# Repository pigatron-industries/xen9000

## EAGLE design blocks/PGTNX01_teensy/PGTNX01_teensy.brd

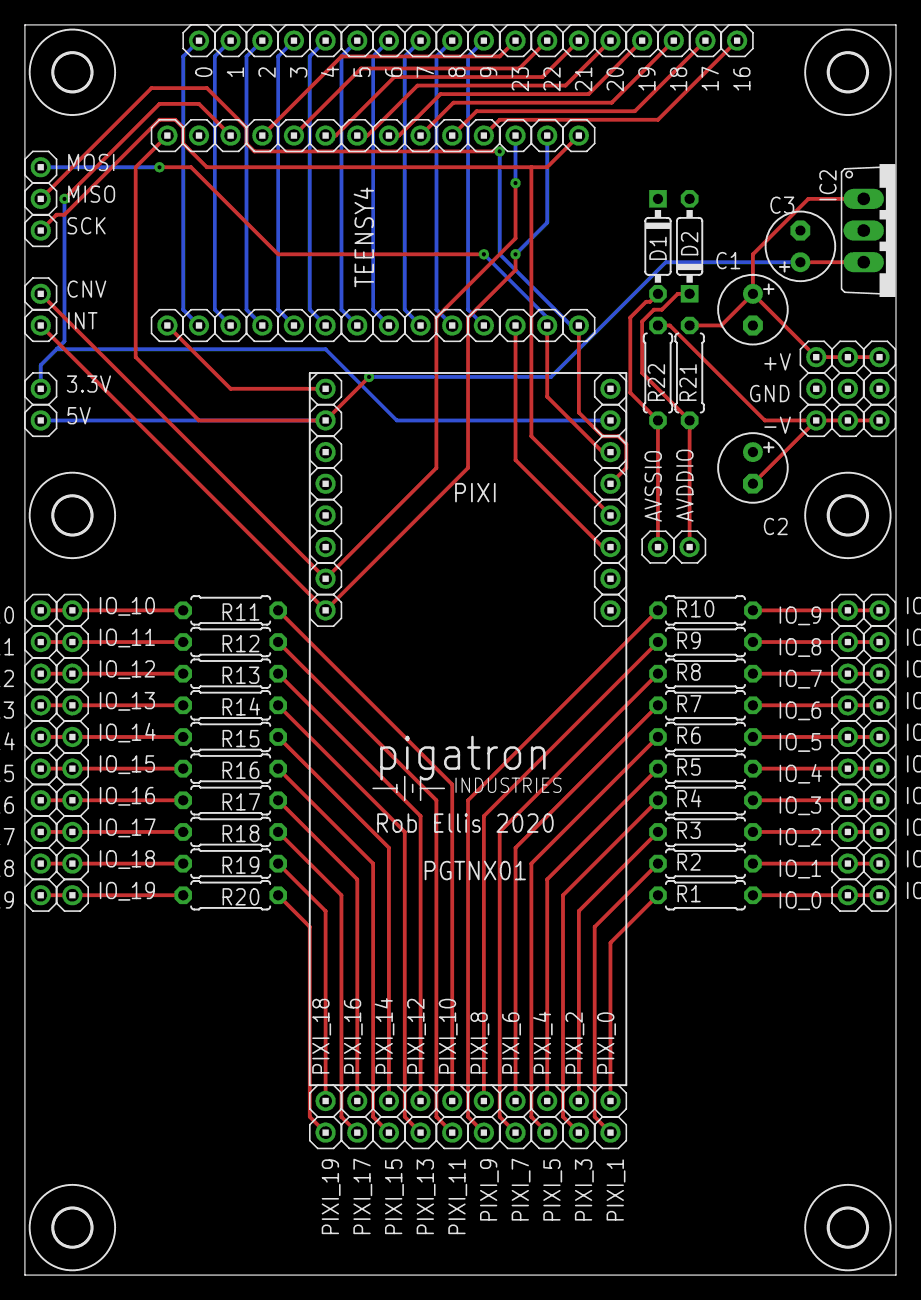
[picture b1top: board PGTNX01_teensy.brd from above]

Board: 2 copper layers, 69.9 x 100.3 mm, 175 parts (0 on the bottom side), 71 nets.

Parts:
0, 1, 2, 3, 3.3V, 4, 5, 5V, 6, 7, 8, 9, 16, 17, 18, 19, 20, 21, 22, 23: HEADER/MALE/01
+V, +V2, +V3: HEADER/MALE/01
-V, -V2, -V3: HEADER/MALE/01
AVDDIO: HEADER/MALE/01
AVSSIO: HEADER/MALE/01
C1, C2: 10uF; E2,5-6
C3: 0.1uF; E2,5-6
CNV: HEADER/MALE/01
D1, D2: DO35-7
GND, GND2, GND3: HEADER/MALE/01
IC2: 7805TV; TO220V
INT: HEADER/MALE/01
IO_0, IO_1, IO_2, IO_3, IO_4, IO_5, IO_6, IO_7, IO_8, IO_9, IO_10, IO_11, IO_12, IO_13, IO_14, IO_15, IO_16, IO_17, IO_18, IO_19: HEADER/MALE/01
IO__0, IO__1, IO__2, IO__3, IO__4, IO__5, IO__6, IO__7, IO__8, IO__9, IO__10, IO__11, IO__12, IO__13, IO__14, IO__15, IO__16, IO__17, IO__18, IO__19: HEADER/MALE/01
MISO: HEADER/MALE/01
MOSI: HEADER/MALE/01
PIXI_0, PIXI_1, PIXI_2, PIXI_3, PIXI_3.3V, PIXI_4, PIXI_5, PIXI_5V, PIXI_6, PIXI_7, PIXI_8, PIXI_9, PIXI_10, PIXI_11, PIXI_12, PIXI_13, PIXI_14, PIXI_15, PIXI_16, PIXI_17, PIXI_18, PIXI_19: HEADER/MALE/01
PIXI_CNV: HEADER/MALE/01
PIXI_CS: HEADER/MALE/01
PIXI_GND, PIXI_GND2: HEADER/MALE/01
PIXI_INT: HEADER/MALE/01
PIXI_NC1, PIXI_NC2, PIXI_NC3, PIXI_NC4, PIXI_NC5, PIXI_NC6: HEADER/MALE/01
PIXI_SCK: HEADER/MALE/01
PIXI_SDI: HEADER/MALE/01
PIXI_SDO: HEADER/MALE/01
R1, R2, R3, R4, R5, R6, R7, R8, R9, R10, R11, R12, R13, R14, R15, R16, R17, R18, R19, R20, R21, R22: RESISTOR/7.5
SCK: HEADER/MALE/01
TNSY_0, TNSY_1, TNSY_2, TNSY_3, TNSY_3.3V, TNSY_4, TNSY_5, TNSY_6, TNSY_7, TNSY_8, TNSY_9, TNSY_14, TNSY_15, TNSY_16, TNSY_17, TNSY_18, TNSY_19, TNSY_20, TNSY_21, TNSY_22, TNSY_23: HEADER/MALE/01
TNSY_CS: HEADER/MALE/01
TNSY_GND, TNSY_GND2: HEADER/MALE/01
TNSY_MISO: HEADER/MALE/01
TNSY_MOSI: HEADER/MALE/01
TNSY_SCK: HEADER/MALE/01
TNSY_VIN: HEADER/MALE/01
U$1, U$2, U$3, U$4, U$6, U$7: STANDOFF/3.0
U$5: PIGATRON-LOGO

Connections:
+5V: 5V.1, C3.+, IC2.3, PIXI_5V.1, TNSY_VIN.1
+12V: +V.1, +V2.1, +V3.1, C1.+, IC2.1, R21.2
-12V: -V.1, -V2.1, -V3.1, C2.-, R22.2
GND: C1.-, C2.+, C3.-, D1.C, D2.A, GND.1, GND2.1, GND3.1, IC2.2, PIXI_GND.1, PIXI_GND2.1, TNSY_GND.1
unnamed: PIXI_0.1, R1.1
unnamed: 17.1, TNSY_17.1
unnamed: PIXI_1.1, R2.1
unnamed: 16.1, TNSY_16.1
unnamed: MOSI.1, PIXI_SDI.1, TNSY_MOSI.1
unnamed: MISO.1, PIXI_SDO.1, TNSY_MISO.1
unnamed: PIXI_SCK.1, SCK.1, TNSY_SCK.1
unnamed: PIXI_CS.1, TNSY_CS.1
unnamed: INT.1, PIXI_CNV.1, TNSY_14.1
unnamed: CNV.1, PIXI_INT.1, TNSY_15.1
unnamed: 18.1, TNSY_18.1
unnamed: 19.1, TNSY_19.1
unnamed: 20.1, TNSY_20.1
unnamed: 21.1, TNSY_21.1
unnamed: 22.1, TNSY_22.1
unnamed: 23.1, TNSY_23.1
unnamed: 0.1, TNSY_0.1
unnamed: 1.1, TNSY_1.1
unnamed: 2.1, TNSY_2.1
unnamed: 3.1, TNSY_3.1
unnamed: 4.1, TNSY_4.1
unnamed: 5.1, TNSY_5.1
unnamed: 6.1, TNSY_6.1
unnamed: 7.1, TNSY_7.1
unnamed: 8.1, TNSY_8.1
unnamed: 9.1, TNSY_9.1
unnamed: IO_1.1, IO__1.1, R2.2
unnamed: 3.3V.1, PIXI_3.3V.1, TNSY_3.3V.1
unnamed: IO_0.1, IO__0.1, R1.2
unnamed: PIXI_2.1, R3.1
unnamed: IO_2.1, IO__2.1, R3.2
unnamed: PIXI_3.1, R4.1
unnamed: IO_3.1, IO__3.1, R4.2
unnamed: PIXI_4.1, R5.1
unnamed: IO_4.1, IO__4.1, R5.2
unnamed: PIXI_5.1, R6.1
unnamed: IO_5.1, IO__5.1, R6.2
unnamed: PIXI_6.1, R7.1
unnamed: IO_6.1, IO__6.1, R7.2
unnamed: PIXI_7.1, R8.1
unnamed: IO_7.1, IO__7.1, R8.2
unnamed: PIXI_8.1, R9.1
unnamed: IO_8.1, IO__8.1, R9.2
unnamed: PIXI_9.1, R10.1
unnamed: IO_9.1, IO__9.1, R10.2
unnamed: PIXI_10.1, R11.1
unnamed: IO_10.1, IO__10.1, R11.2
unnamed: PIXI_11.1, R12.1
unnamed: IO_11.1, IO__11.1, R12.2
unnamed: PIXI_12.1, R13.1
unnamed: IO_12.1, IO__12.1, R13.2
unnamed: PIXI_13.1, R14.1
unnamed: IO_13.1, IO__13.1, R14.2
unnamed: PIXI_14.1, R15.1
unnamed: IO_14.1, IO__14.1, R15.2
unnamed: PIXI_15.1, R16.1
unnamed: IO_15.1, IO__15.1, R16.2
unnamed: PIXI_16.1, R17.1
unnamed: IO_16.1, IO__16.1, R17.2
unnamed: PIXI_17.1, R18.1
unnamed: IO_17.1, IO__17.1, R18.2
unnamed: PIXI_18.1, R19.1
unnamed: IO_18.1, IO__18.1, R19.2
unnamed: PIXI_19.1, R20.1
unnamed: IO_19.1, IO__19.1, R20.2
unnamed: AVDDIO.1, D2.C, R21.1
unnamed: AVSSIO.1, D1.A, R22.1

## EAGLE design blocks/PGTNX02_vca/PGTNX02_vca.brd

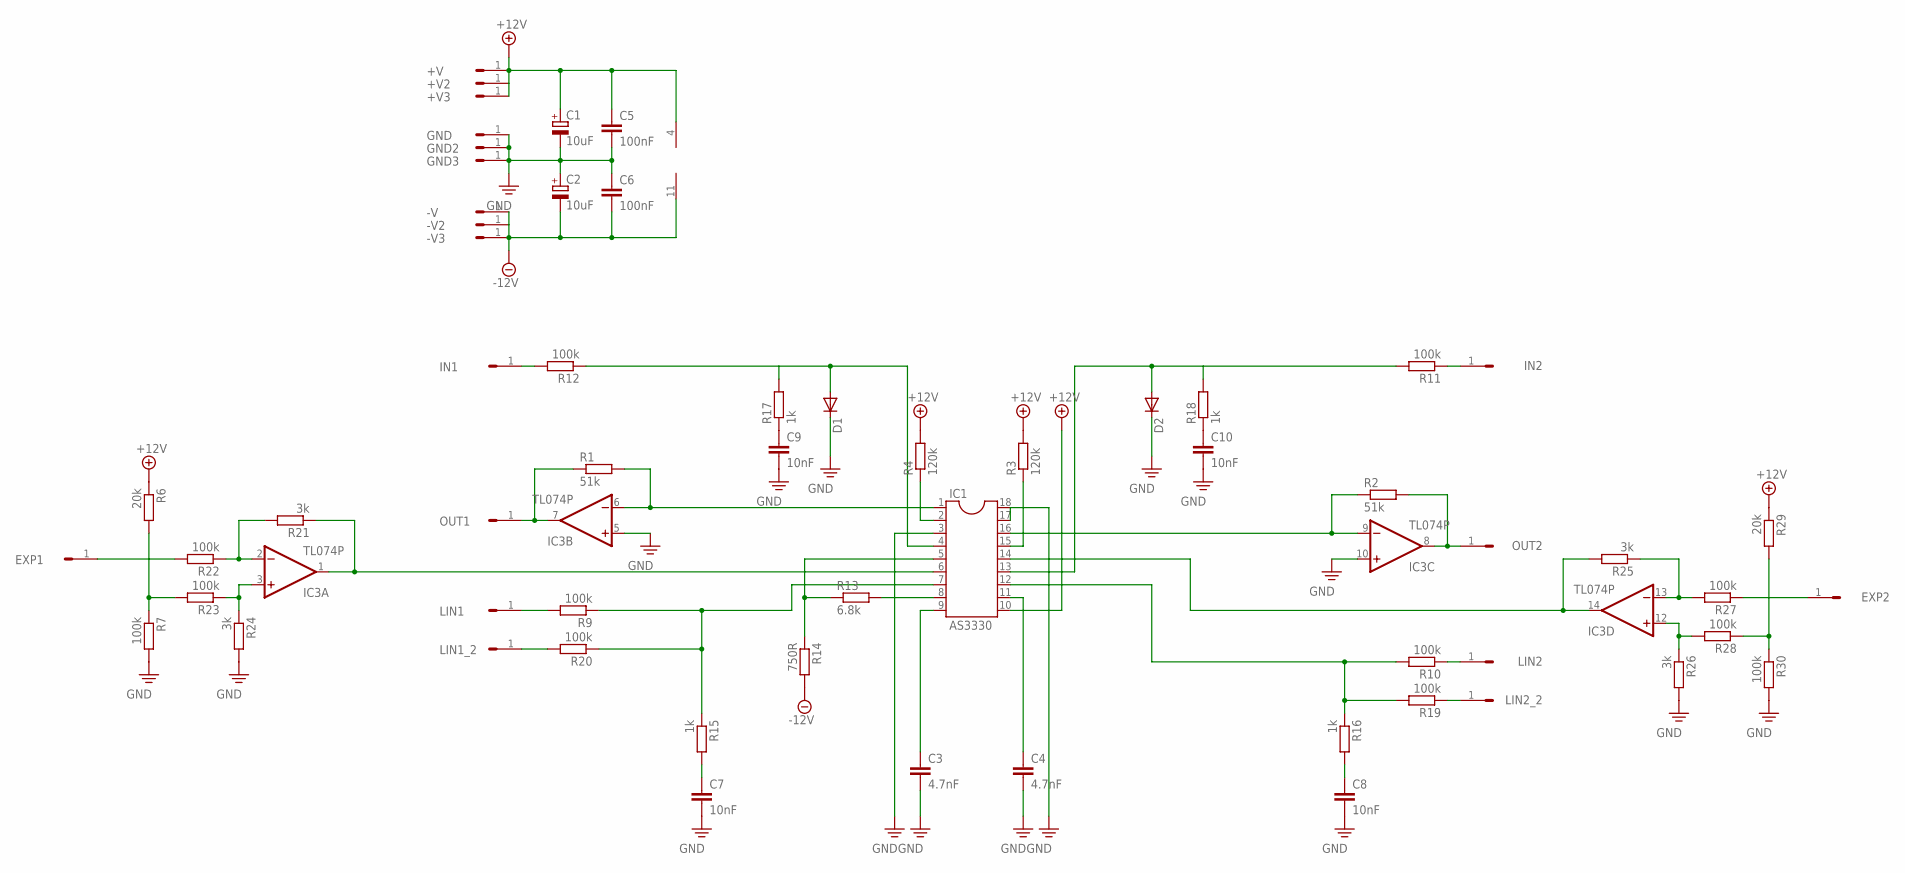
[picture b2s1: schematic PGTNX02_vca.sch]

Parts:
+V, +V2, +V3: HEADER/MALE/01
-V, -V2, -V3: HEADER/MALE/01
C1, C2: 10uF; E2,5-6
C3, C4: 4.7nF; CERAMICDISC/5
C5, C6: 100nF; CERAMICDISC/5
C7, C8, C9, C10: 10nF; CERAMICDISC/5
D1, D2: 1N4148DO35-7; DO35-7
EXP1, EXP2: HEADER/MALE/01
GND, GND2, GND3: HEADER/MALE/01
IC1: AS3330; DIL18
IC3: TL074P; DIL14
IN1, IN2: HEADER/MALE/01
LIN1, LIN1_2, LIN2, LIN2_2: HEADER/MALE/01
OUT1, OUT2: HEADER/MALE/01
R1, R2: 51k; RESISTOR/7.5
R3, R4: 120k; RESISTOR/7.5
R6, R29: 20k; RESISTOR/7.5
R7, R9, R10, R11, R12, R19, R20, R22, R23, R27, R28, R30: 100k; RESISTOR/7.5
R13: 6.8k; RESISTOR/7.5
R14: 750R; RESISTOR/7.5
R15, R16, R17, R18: 1k; RESISTOR/7.5
R21, R24, R25, R26: 3k; RESISTOR/7.5

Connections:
+12V: +V.1, +V2.1, +V3.1, C1.+, C5.1, IC1.10, IC3.4 (V+), R3.2, R4.2, R6.1, R29.1
-12V: -V.1, -V2.1, -V3.1, C2.-, C6.2, IC3.11 (V-), R14.2
unnamed: IC1.1, IC3.6 (-IN), R1.2
unnamed: IC3.7 (OUT), OUT1.1, R1.1
unnamed: IC1.16, IC3.9 (-IN), R2.1
unnamed: IC3.8 (OUT), OUT2.1, R2.2
unnamed: C4.1, IC1.11
unnamed: IC1.15, R3.1
unnamed: IC1.2, R4.1
unnamed: C3.1, IC1.9
unnamed: IC1.14, IC3.14 (OUT), R25.2
unnamed: IC1.6, IC3.1 (OUT), R21.1
unnamed: EXP1.1, R22.2
unnamed: EXP2.1, R27.1
unnamed: IC1.7, R9.1, R15.1, R20.1
unnamed: IC1.12, R10.2, R16.1, R19.2
unnamed: LIN2.1, R10.1
unnamed: LIN1.1, R9.2
unnamed: D2.A, IC1.13, R11.2, R18.2
unnamed: D1.A, IC1.4, R12.1, R17.2
unnamed: IN1.1, R12.2
unnamed: IN2.1, R11.1
unnamed: IC1.5, R13.1, R14.1
unnamed: IC1.8, R13.2
unnamed: C7.1, R15.2
unnamed: C8.1, R16.2
unnamed: C9.1, R17.1
unnamed: C10.1, R18.1
unnamed: LIN1_2.1, R20.2
unnamed: LIN2_2.1, R19.1
unnamed: R6.2, R7.1, R23.2
unnamed: IC3.2 (-IN), R21.2, R22.1
unnamed: IC3.3 (+IN), R23.1, R24.1
unnamed: IC3.13 (-IN), R25.1, R27.2
unnamed: IC3.12 (+IN), R26.1, R28.2
unnamed: R28.1, R29.2, R30.1
PE: C1.-, C2.+, C3.2, C4.2, C5.2, C6.1, C7.2, C8.2, C9.2, C10.2, D1.C, D2.C, GND.1, GND2.1, GND3.1, IC1.3, IC1.17, IC1.18, IC3.5 (+IN), IC3.10 (+IN), R7.2, R24.2, R26.2, R30.2

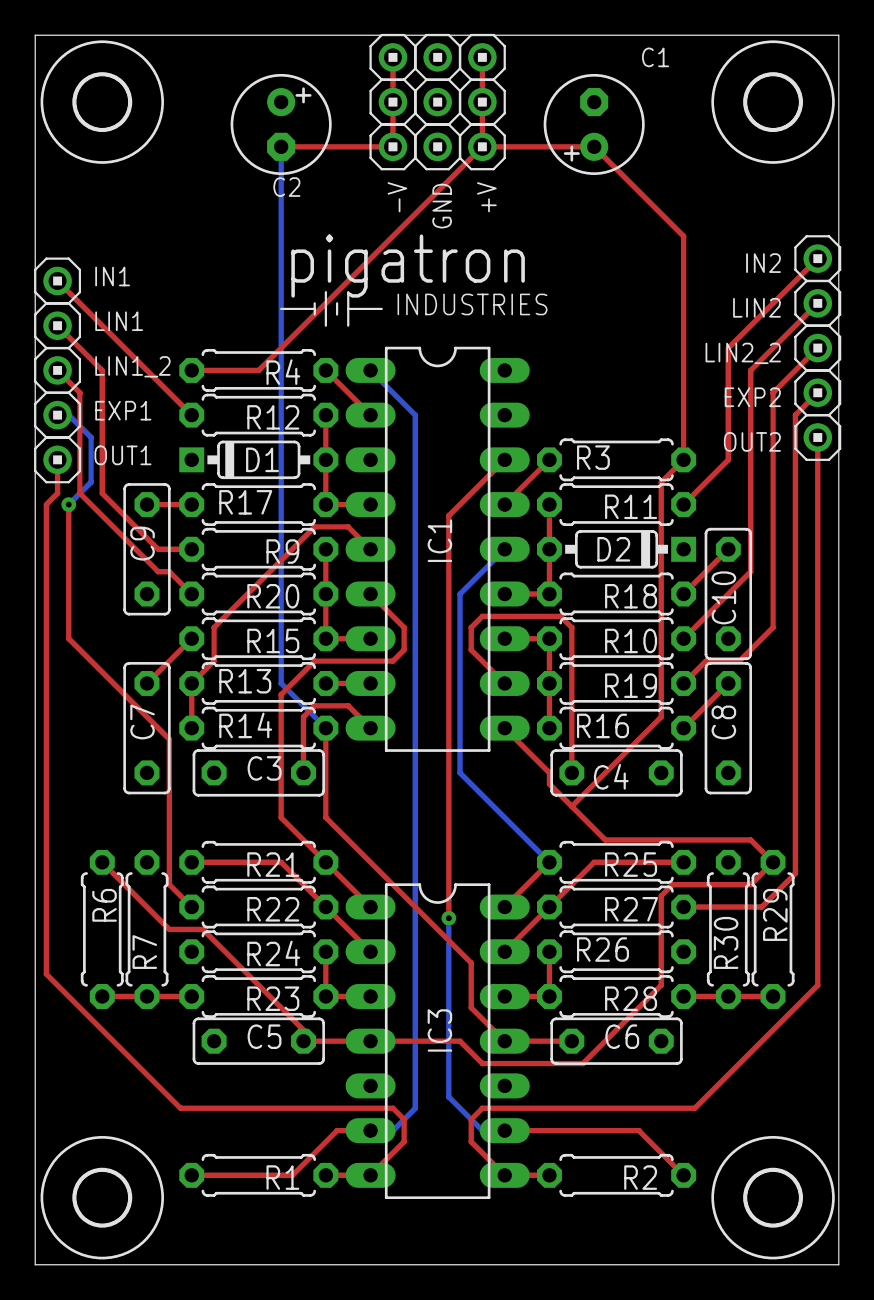
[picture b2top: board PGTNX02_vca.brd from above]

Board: 2 copper layers, 45.6 x 69.8 mm, 66 parts (0 on the bottom side), 37 nets.

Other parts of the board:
U$1, U$2, U$3, U$4: STANDOFF/3.0
U$5: PIGATRON-LOGO

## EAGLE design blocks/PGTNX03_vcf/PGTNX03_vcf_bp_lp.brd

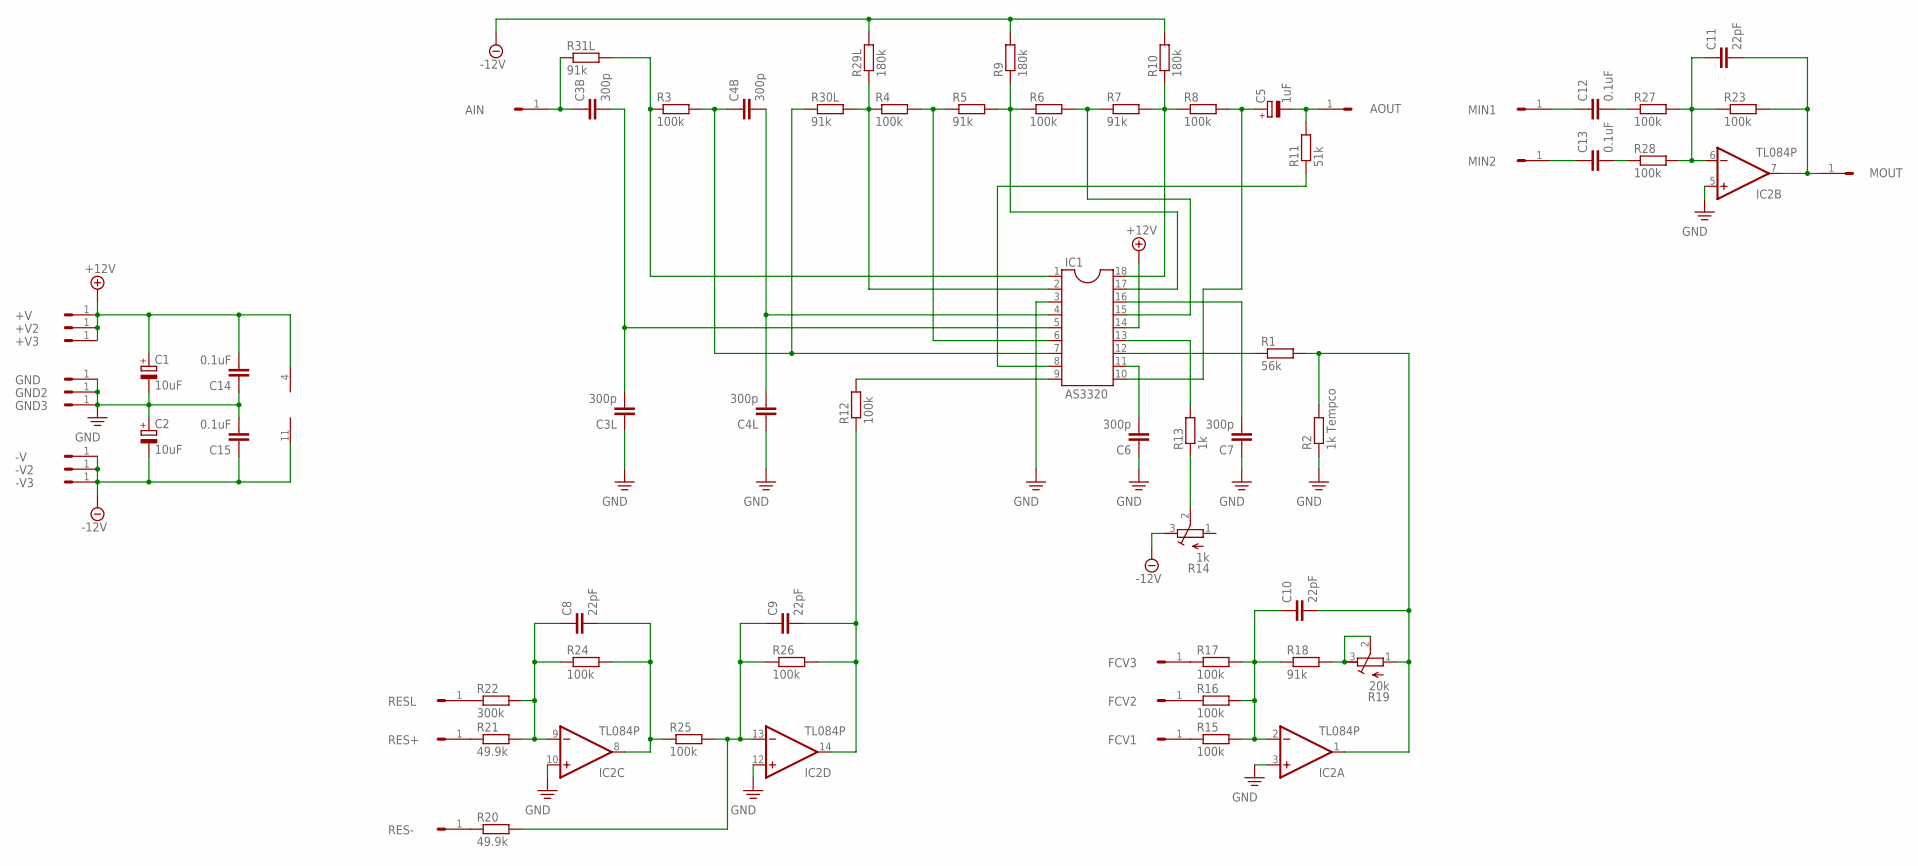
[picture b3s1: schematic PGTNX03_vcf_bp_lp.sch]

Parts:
+V, +V2, +V3: HEADER/MALE/01
-V, -V2, -V3: HEADER/MALE/01
AIN: HEADER/MALE/01
AOUT: HEADER/MALE/01
C1, C2: 10uF; E2,5-6
C3B, C3L, C4B, C4L, C6, C7: 300p; CERAMICDISC/5
C5: 1uF; E2,5-6
C8, C9, C10, C11: 22pF; CERAMICDISC/5
C12, C13, C14, C15: 0.1uF; CERAMICDISC/5
FCV1, FCV2, FCV3: HEADER/MALE/01
GND, GND2, GND3: HEADER/MALE/01
IC1: AS3320; DIL18
IC2: TL084P; DIL14
MIN1, MIN2: HEADER/MALE/01
MOUT: HEADER/MALE/01
R1: 56k; RESISTOR/7.5
R2: 1k Tempco; RESISTOR/7.5
R3, R4, R6, R8, R12, R15, R16, R17, R23, R24, R25, R26, R27, R28: 100k; RESISTOR/7.5
R5, R7, R18, R30L, R31L: 91k; RESISTOR/7.5
R9, R10, R29L: 180k; RESISTOR/7.5
R11: 51k; RESISTOR/7.5
R13: 1k; RESISTOR/7.5
R14: 1k; TRIMMER/64B
R19: 20k; TRIMMER/64B
R20, R21: 49.9k; RESISTOR/7.5
R22: 300k; RESISTOR/7.5
RES+: HEADER/MALE/01
RES-: HEADER/MALE/01
RESL: HEADER/MALE/01

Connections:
+12V: +V.1, +V2.1, +V3.1, C1.+, C14.2, IC1.14, IC2.4 (V+)
-12V: -V.1, -V2.1, -V3.1, C2.-, C15.1, IC2.11 (V-), R9.2, R10.2, R14.3 (A), R29L.2
GND: C1.-, C2.+, C3L.1, C4L.1, C6.1, C7.1, C14.1, C15.2, GND.1, GND2.1, GND3.1, IC1.3, IC2.3 (+IN), IC2.5 (+IN), IC2.10 (+IN), IC2.12 (+IN), R2.1
MOUT: C11.2, IC2.7 (OUT), MOUT.1, R23.2
unnamed: C3B.2, C3L.2, IC1.5
unnamed: AIN.1, C3B.1, R31L.1
unnamed: IC1.12, R1.1
unnamed: R20.1, RES-.1
unnamed: C4B.1, IC1.7, R3.2, R30L.1
unnamed: IC1.6, R4.2, R5.1
unnamed: IC1.17, R5.2, R6.1, R9.1
unnamed: IC1.15, R6.2, R7.1
unnamed: IC1.18, R7.2, R8.1, R10.1
unnamed: IC1.9, R12.2
unnamed: C5.+, IC1.10, R8.2
unnamed: AOUT.1, C5.-, R11.2
unnamed: R18.2, R19.2 (S), R19.3 (A)
unnamed: C6.2, IC1.11
unnamed: C7.2, IC1.16
unnamed: FCV2.1, R16.1
unnamed: FCV3.1, R17.1
unnamed: IC1.13, R13.2
unnamed: R13.1, R14.2 (S)
unnamed: IC1.1, R3.1, R31L.2
unnamed: C4B.2, C4L.2, IC1.4
unnamed: IC1.2, R4.1, R29L.1, R30L.2
unnamed: IC1.8, R11.1
unnamed: C10.2, IC2.1 (OUT), R1.2, R2.2, R19.1 (E)
unnamed: C10.1, IC2.2 (-IN), R15.2, R16.2, R17.2, R18.1
unnamed: C12.2, R27.1
unnamed: FCV1.1, R15.1
unnamed: C11.1, IC2.6 (-IN), R23.1, R27.2, R28.2
unnamed: C8.1, IC2.9 (-IN), R21.2, R22.2, R24.1
unnamed: R21.1, RES+.1
unnamed: R22.1, RESL.1
unnamed: C13.2, R28.1
unnamed: C8.2, IC2.8 (OUT), R24.2, R25.1
unnamed: C9.1, IC2.13 (-IN), R20.2, R25.2, R26.1
unnamed: C9.2, IC2.14 (OUT), R12.1, R26.2
unnamed: C12.1, MIN1.1
unnamed: C13.1, MIN2.1

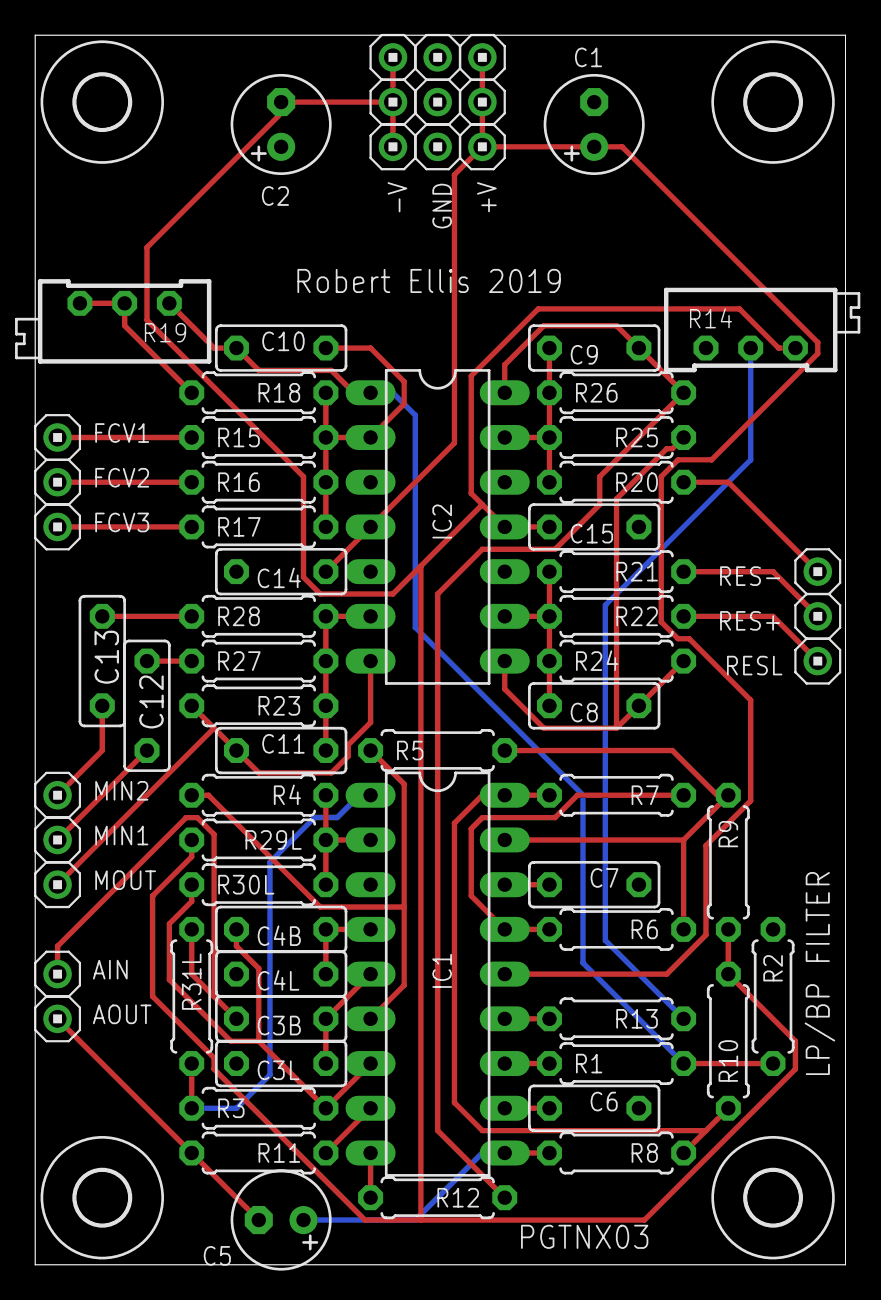
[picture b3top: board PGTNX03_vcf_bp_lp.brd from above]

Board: 2 copper layers, 46.0 x 69.8 mm, 75 parts (1 on the bottom side), 41 nets.

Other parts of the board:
U$1, U$2, U$3, U$4: STANDOFF/3.0
U$6: PIGATRON-LOGO

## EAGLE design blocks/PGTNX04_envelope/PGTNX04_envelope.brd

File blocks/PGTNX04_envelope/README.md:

# History

## V1
* Labelled PGTN020B
* C7 not connected to ground plane. Kludge by scraping away solder mask next to it and adding solder bridge.

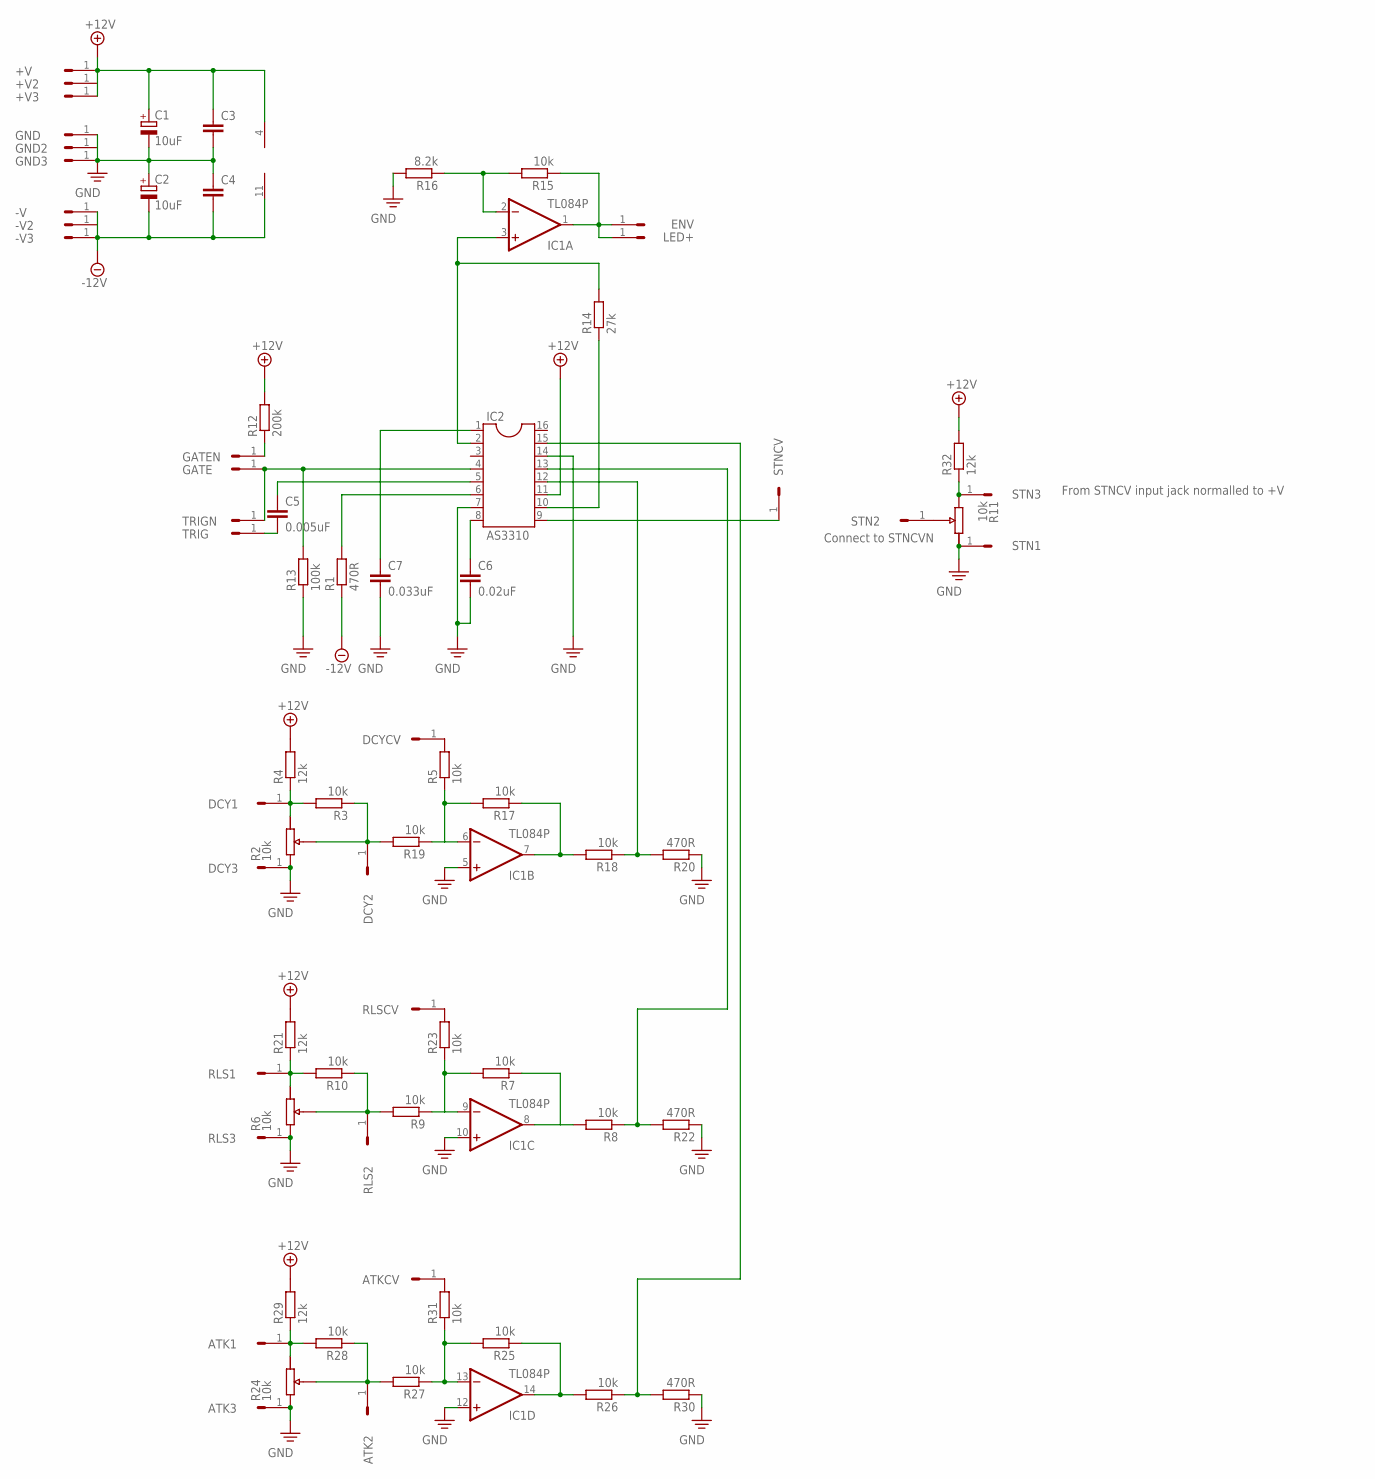
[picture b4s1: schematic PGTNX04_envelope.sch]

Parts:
+V, +V2, +V3: HEADER/MALE/01
-V, -V2, -V3: HEADER/MALE/01
ATK1, ATK2, ATK3: HEADER/MALE/01
ATKCV: HEADER/MALE/01
C1, C2: 10uF; E2,5-6
C3, C4: CAPACITORCERAMICDISC/5; CERAMICDISC/5
C5: 0.005uF; CERAMICDISC/5
C6: 0.02uF; CERAMICDISC/5
C7: 0.033uF; CERAMICDISC/5
DCY1, DCY2, DCY3: HEADER/MALE/01
DCYCV: HEADER/MALE/01
ENV: HEADER/MALE/01
GATE: HEADER/MALE/01
GATEN: HEADER/MALE/01
GND, GND2, GND3: HEADER/MALE/01
IC1: TL084P; DIL14
IC2: AS3310; DIL16
LED+: HEADER/MALE/01
R1, R20, R22, R30: 470R; RESISTOR/7.5
R3, R5, R7, R8, R9, R10, R15, R17, R18, R19, R23, R25, R26, R27, R28, R31: 10k; RESISTOR/7.5
R4, R21, R29, R32: 12k; RESISTOR/7.5
R12: 200k; RESISTOR/7.5
R13: 100k; RESISTOR/7.5
R14: 27k; RESISTOR/7.5
R16: 8.2k; RESISTOR/7.5
RLS1, RLS2, RLS3: HEADER/MALE/01
RLSCV: HEADER/MALE/01
STN1, STN2, STN3: HEADER/MALE/01
STNCV: HEADER/MALE/01
TRIG: HEADER/MALE/01
TRIGN: HEADER/MALE/01

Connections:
+12V: +V.1, +V2.1, +V3.1, C1.+, C3.1, IC1.4 (V+), IC2.11, R4.2, R12.2, R21.2, R29.2, R32.2
-12V: -V.1, -V2.1, -V3.1, C2.-, C4.2, IC1.11 (V-), R1.1
GND: ATK3.1, C1.-, C2.+, C3.2, C4.1, C6.2, C7.2, DCY3.1, GND.1, GND2.1, GND3.1, IC1.5 (+IN), IC1.10 (+IN), IC1.12 (+IN), IC2.7, IC2.14, R13.1, R16.2, R20.1, R22.1, R30.1, RLS3.1, STN1.1
unnamed: IC2.9, STNCV.1
unnamed: GATEN.1, R12.1
unnamed: C5.1, IC2.5
unnamed: GATE.1, IC2.4, R13.2, TRIGN.1
unnamed: DCYCV.1, R5.2
unnamed: IC1.8 (OUT), R7.1, R8.2
unnamed: IC1.9 (-IN), R7.2, R9.1, R23.1
unnamed: R9.2, R10.1, RLS2.1
unnamed: C5.2, TRIG.1
unnamed: R10.2, R21.1, RLS1.1
unnamed: IC2.13, R8.1, R22.2
unnamed: IC2.6, R1.2
unnamed: C6.1, IC2.8
unnamed: C7.1, IC2.1
unnamed: IC1.2 (-IN), R15.2, R16.1
unnamed: IC2.10, R14.1
unnamed: IC1.3 (+IN), IC2.2, R14.2
unnamed: ENV.1, IC1.1 (OUT), LED+.1, R15.1
unnamed: IC1.7 (OUT), R17.1, R18.2
unnamed: IC1.6 (-IN), R5.1, R17.2, R19.1
unnamed: DCY2.1, R3.1, R19.2
unnamed: IC2.12, R18.1, R20.2
unnamed: DCY1.1, R3.2, R4.1
unnamed: R23.2, RLSCV.1
unnamed: IC1.14 (OUT), R25.1, R26.2
unnamed: IC1.13 (-IN), R25.2, R27.1, R31.1
unnamed: ATK2.1, R27.2, R28.1
unnamed: ATK1.1, R28.2, R29.1
unnamed: IC2.15, R26.1, R30.2
unnamed: ATKCV.1, R31.2
unnamed: R32.1, STN3.1

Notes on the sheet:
Connect to STNCVN
From STNCV input jack normalled to +V

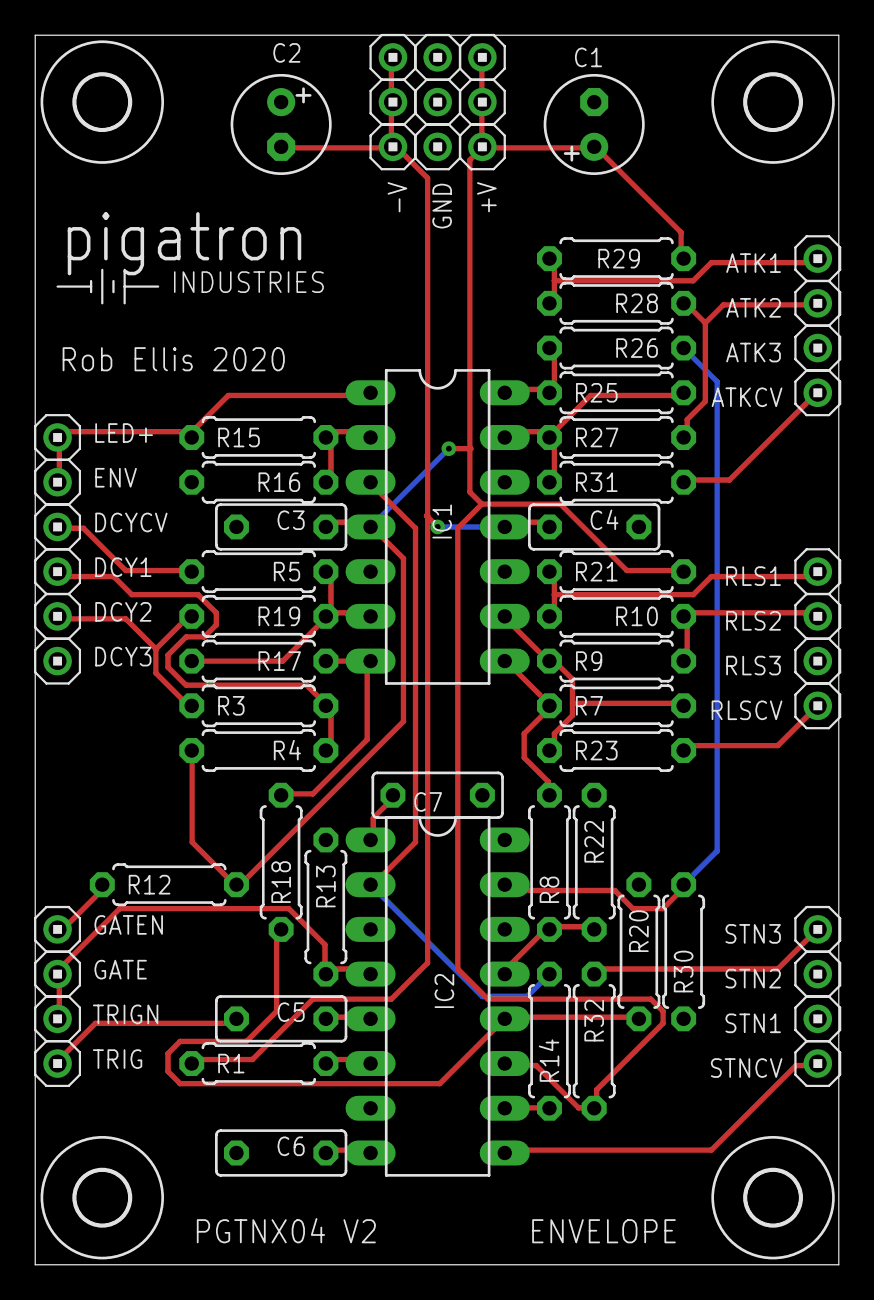
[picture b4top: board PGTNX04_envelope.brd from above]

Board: 2 copper layers, 45.6 x 69.8 mm, 73 parts (0 on the bottom side), 34 nets.

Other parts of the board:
U$1, U$2, U$3, U$4: STANDOFF/3.0
U$5: PIGATRON-LOGO
